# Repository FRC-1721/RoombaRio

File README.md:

# Roomba Rio

A rp3 backpack for the 500 series roombas!

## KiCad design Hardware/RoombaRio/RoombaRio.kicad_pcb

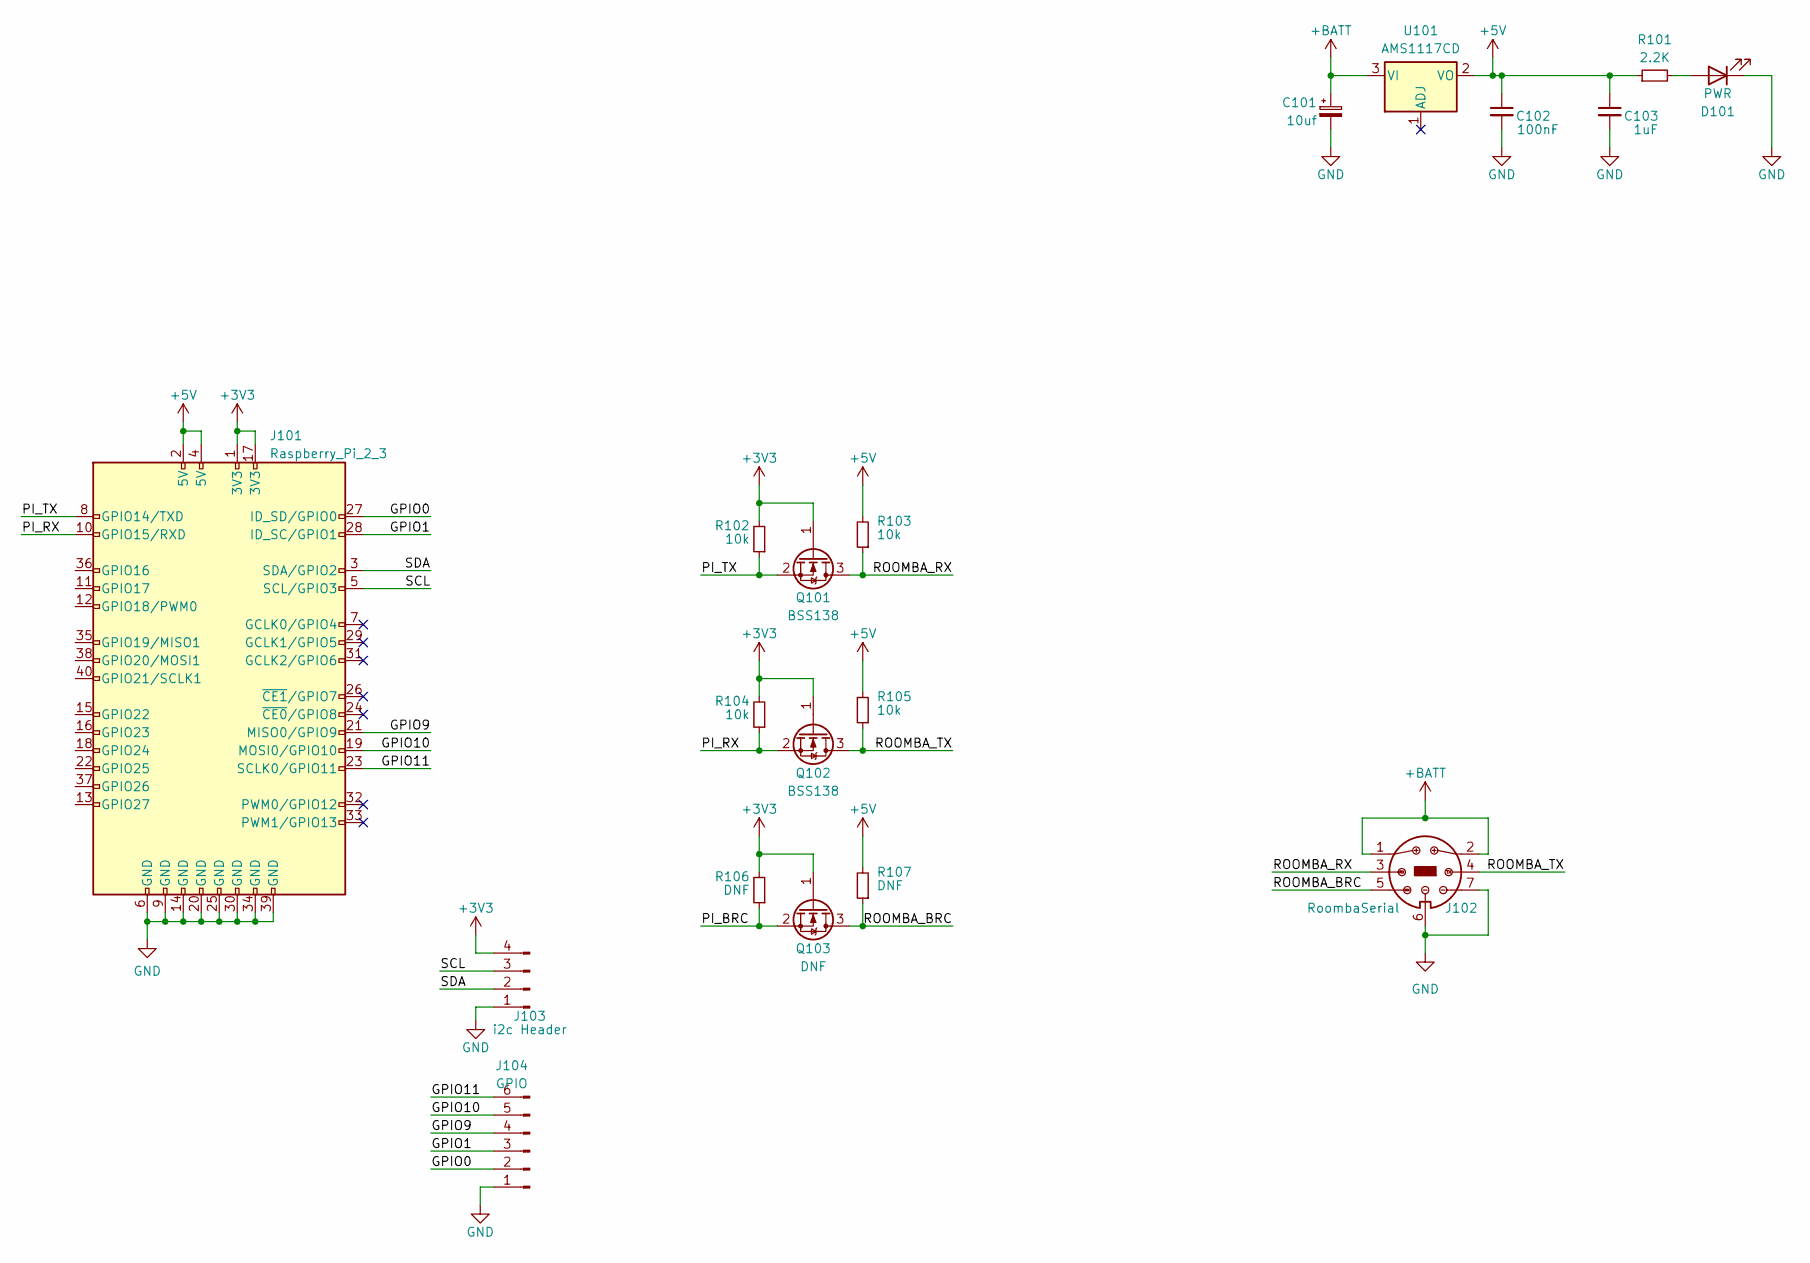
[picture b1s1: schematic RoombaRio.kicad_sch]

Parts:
C101: 10uf; CP_Elec_4x3; LCSC C98746
C102: 100nF; C_0805_2012Metric
C103: 1uF; C_0805_2012Metric
D101: PWR; LED_0805_2012Metric
J101: Raspberry_Pi_2_3; PinHeader_2x20_P2.54mm_Vertical
J102: RoombaSerial; Roomba7Pin
J103: i2c Header; JST_XH_S4B-XH-A_1x04_P2.50mm_Horizontal
J104: GPIO; JST_XH_S6B-XH-A_1x06_P2.50mm_Horizontal
Q101, Q102: BSS138; SOT-23
Q103: DNF; SOT-23
R101: 2.2K; R_0805_2012Metric
R102, R103, R104, R105: 10k; R_0805_2012Metric
R106, R107: DNF; R_0805_2012Metric
U101: AMS1117CD; TO-252-3_TabPin2; LCSC C347250

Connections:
+3V3: J101.1 (3V3), J101.17 (3V3), J103.4, Q101.1 (G), Q102.1 (G), Q103.1 (G), R102.2, R104.2, R106.2
+5V: C102.1, C103.1, J101.2 (5V), J101.4 (5V), R101.1, R103.2, R105.2, R107.2, U101.2 (VO)
+BATT: C101.1, J102.1, J102.2, U101.3 (VI)
/GPIO0: J101.27 (ID_SD/GPIO0), J104.2
/GPIO1: J101.28 (ID_SC/GPIO1), J104.3
/GPIO9: J101.21 (MISO0/GPIO9), J104.4
/GPIO10: J101.19 (MOSI0/GPIO10), J104.5
/GPIO11: J101.23 (SCLK0/GPIO11), J104.6
/PI_BRC: Q103.2 (S), R106.1
/PI_RX: J101.10 (GPIO15/RXD), Q102.2 (S), R104.1
/PI_TX: J101.8 (GPIO14/TXD), Q101.2 (S), R102.1
/ROOMBA_BRC: J102.5, Q103.3 (D), R107.1
/ROOMBA_RX: J102.3, Q101.3 (D), R103.1
/ROOMBA_TX: J102.4, Q102.3 (D), R105.1
/SCL: J101.5 (SCL/GPIO3), J103.3
/SDA: J101.3 (SDA/GPIO2), J103.2
GND: C101.2, C102.2, C103.2, D101.1 (K), J101.6 (GND), J101.9 (GND), J101.14 (GND), J101.20 (GND), J101.25 (GND), J101.30 (GND), J101.34 (GND), J101.39 (GND), J102.6, J102.7, J103.1, J104.1
unnamed: D101.2 (A), R101.2

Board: 2 copper layers, 19 parts (0 on the bottom side), 18 nets, no tracks yet.

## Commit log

2023-04-30 init to commit it
2023-05-11 Layout the basic roomba plug symbol
2023-05-13 Add inital edge cuts and upstream roomba improvements
2023-05-16 Inital power mgmnt
2023-05-16 off to robotics
